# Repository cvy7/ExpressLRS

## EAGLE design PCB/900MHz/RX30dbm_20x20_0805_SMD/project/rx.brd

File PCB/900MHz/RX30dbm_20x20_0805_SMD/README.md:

# 20x38 RX30dbm PCB

## Features

 * 20x38 footprint
 * 0805 size SMD components (for easy soldering) - NOTE: LED is still 0603 as this size is more common in LEDs
 * Components are placed for ease of soldering (easy iron access)
 * u.fl antenna connector footprint for 915MHz antenna
 * PCB trace antenna for WiFi
 * 5V input 
 * RFM95PW-868S2 with Output power +27dBm

## Editing

 * The PCB has been developed in Eagle, and the custom libraries that were used are attached in the /lib directory. Copy the project files into you Eagle project dir, and the libs into your lib dir, then fire up Eagle and edit.

 ## Ordering

 * I've had good results using JLCPCB (https://jlcpcb.com/). Upload the .zip file in this repo and adjust any PCB parameters that you want (defaults work fine).
 * A super-lightweight build can be achieved by going to a 0.6mm PCB thickness (without an increase to cost)

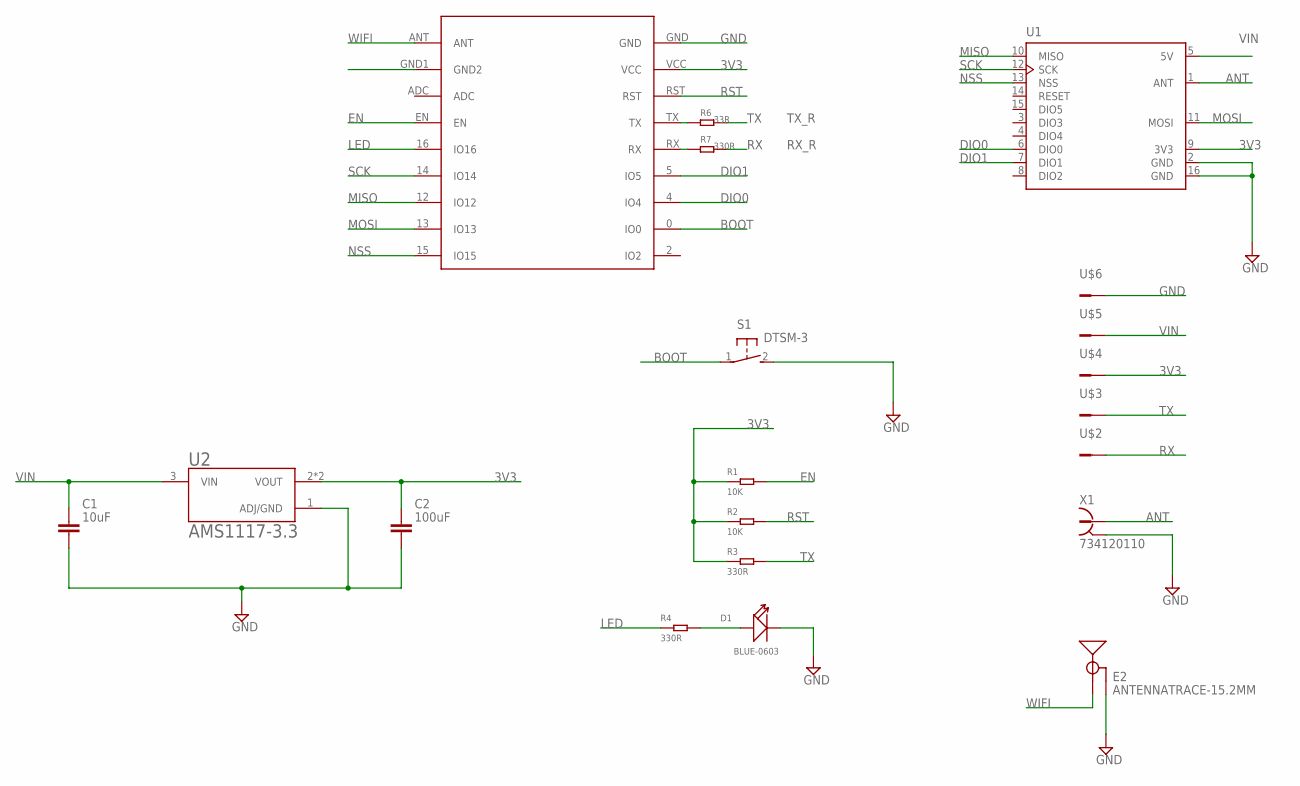
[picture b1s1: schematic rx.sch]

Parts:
C1: 10uF; CAPM3528X210
C2: 100uF; CAPM3528X210
D1: BLUE-0603; LED-0603
E2: ANTENNATRACE-15.2MM; TRACE_ANTENNA_2.4GHZ_15.2MM
R1, R2: 10K; R0805
R3, R4, R7: 330R; R0805
R6: 33R; R0805
S1: DTSM-3
U1: RFM95PW-868S2PW; XCVR_RFM95PW-868S2
U2: AMS1117-3.3; SOT229P700X180-4N
U$1: ESP-M2
U$2, U$3, U$4, U$5, U$6: CONN-1; PAD1
X1: 734120110

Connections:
3V3: C2.1, R1.1, R2.1, R3.1, U1.9 (3V3), U2.2 (VOUT), U2.4 (VOUT), U$1.VCC, U$4.P$1
ANT: U1.1 (ANT), X1.1
BOOT: S1.1, U$1.0 (IO0)
DIO0: U1.6 (DIO0), U$1.4 (IO4)
DIO1: U1.7 (DIO1), U$1.5 (IO5)
EN: R1.2, U$1.EN
GND: C1.2, C2.2, D1.-, E2.GND, S1.2, U1.2 (GND), U1.16 (GND), U2.1 (ADJ/GND), U$1.GND, U$1.GND1 (GND2), U$6.P$1, X1.S@1 (2), X1.S@2 (2), X1.S@3 (2)
LED: R4.1, U$1.16 (IO16)
MISO: U1.10 (MISO), U$1.12 (IO12)
MOSI: U1.11 (MOSI), U$1.13 (IO13)
unnamed: D1.+, R4.2
NSS: U1.13 (NSS), U$1.15 (IO15)
RST: R2.2, U$1.RST
RX: R7.2, U$2.P$1
RX_R: R7.1, U$1.RX
SCK: U1.12 (SCK), U$1.14 (IO14)
TX: R3.2, R6.2, U$3.P$1
TX_R: R6.1, U$1.TX
VIN: C1.1, U1.5 (5V), U2.3 (VIN), U$5.P$1
WIFI: E2.ANT (SIGNAL), U$1.ANT

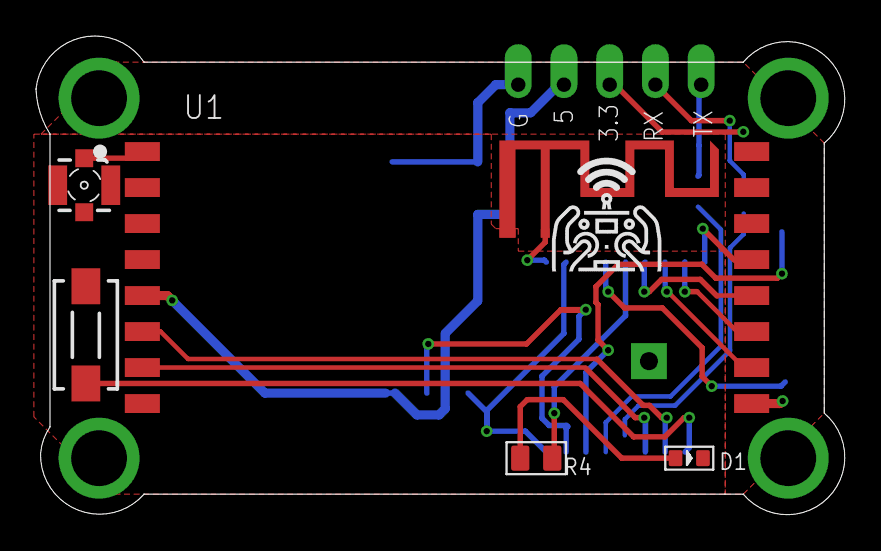
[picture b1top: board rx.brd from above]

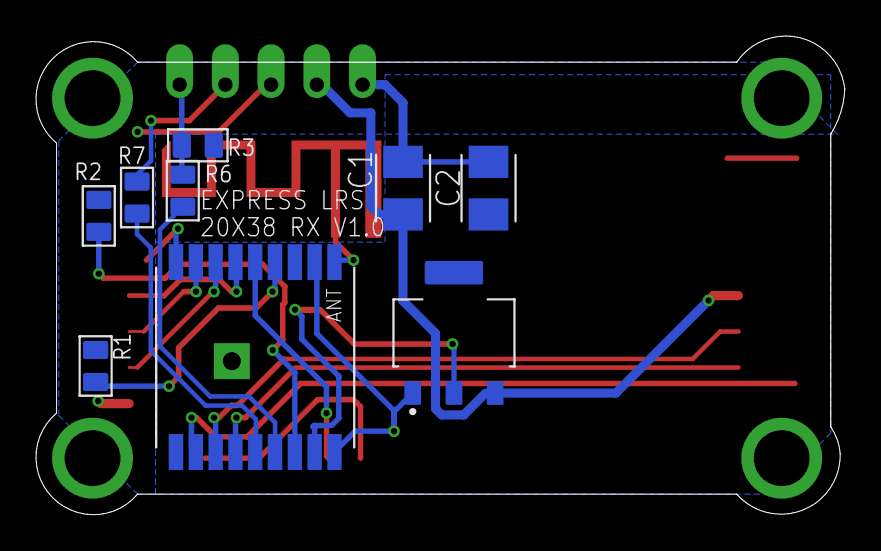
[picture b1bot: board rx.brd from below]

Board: 2 copper layers, 44.9 x 26.6 mm, 20 parts (9 on the bottom side), 20 nets.

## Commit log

2021-02-21 added rx pcb with rfm95pw
